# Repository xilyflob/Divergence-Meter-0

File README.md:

# Purpose
Recreate Tom Titor's original Divergence Meter project with more up to date hardware and software. Also taking into account current tools and services avalible to makers.

# Goals
* Maintain level of visual accuracy to the show that was in the original.
* Keep code size down so if people don't want to use updated hardware they can still fit it on the old chip.
  * Currently failing this, assembly output from the C code has proven much less efficient than I had anticipated.
* Provide more accessible code for the microcontroller so makers can make changes on their own easier than with the assembly version, also commented well enough that it is easy to understand.
* Produce at least proper drawings for the physical construction. Ideally a solid model as well, however there may be license issues with that.

# Software Used
* Autodesk Eagle
  * Originally used to do the PCB design, the SMT versions were later converted to KiCad. Earlier, simpler converts and redesigns currently remain in those file types.
* KiCad
* MPLAB X IDE
  * XC8 compiler
* Solidworks

# Build Log
Available on [Imgur](https://imgur.com/a/QL4b4lS), maybe one day I will make a website for better layout and such.

# Current Status 9/16/23
Long time no update :)

Lost lots of motivation to work on this after I realized that there are more I2C issues. Regular writes flat out dont work, you make it though the code but they don't take on the RTC. Currently implementing a fix that is reccomended in the 8803 manual, hopefully it works.

No changes to hardware this time, I do have a bunch of ideas for a Rev B including actually hooking up the INT line from the RTC which could prove EXTREMELY useful in making the software less "busy".

Motivation remains hard, hope to keep at this as well as I can.

# Background
Full disclosure time, I have zero formal training in coding or electrical engineering, I am actually a machinist (I guess that makes me qualified to fab the actual box though). On top of this, this is my first time doing any assembly reading, C coding, coding for microchips, or circuit board design. If I make a mistake that you see, PLEASE tell me.

I've wanted to do Tom's divergence meter project basically since I first found it after watching the Steins;Gate show. Never actually had the drive to do it though. Don't ask me why, but at some point in 2021 I went to look at the site, only to find it gone. Wayback Machine has an archive, but more importantly whoever the saint is that runs brotoro.com made a complete functional rehost of the site, which is much less clunky than Wayback. Would definitely say that almost losing that info really pushed me to start working on this.

# Thanks
* Jonathan from [SWISSNIXIE](http://www.swissnixie.com/) for helping me understand nixie tube amperage and resistance requirement as well as lending prototyping advice on the HV5623 drivers.
* John from [Taylor Electronics](https://www.shop-tes.com/) for providing data on the current usage of the 1364 HVPS in this specific application.
* /r/PrintedCircuitBoard for doing their best to answer my questions

# Licence
Hardware: Creative Commons Attribution-ShareAlike 4.0 International

Software: GNU GPL V3.0

Also just let me know if you use anything. Or if you make this! Would love to see people's projects.

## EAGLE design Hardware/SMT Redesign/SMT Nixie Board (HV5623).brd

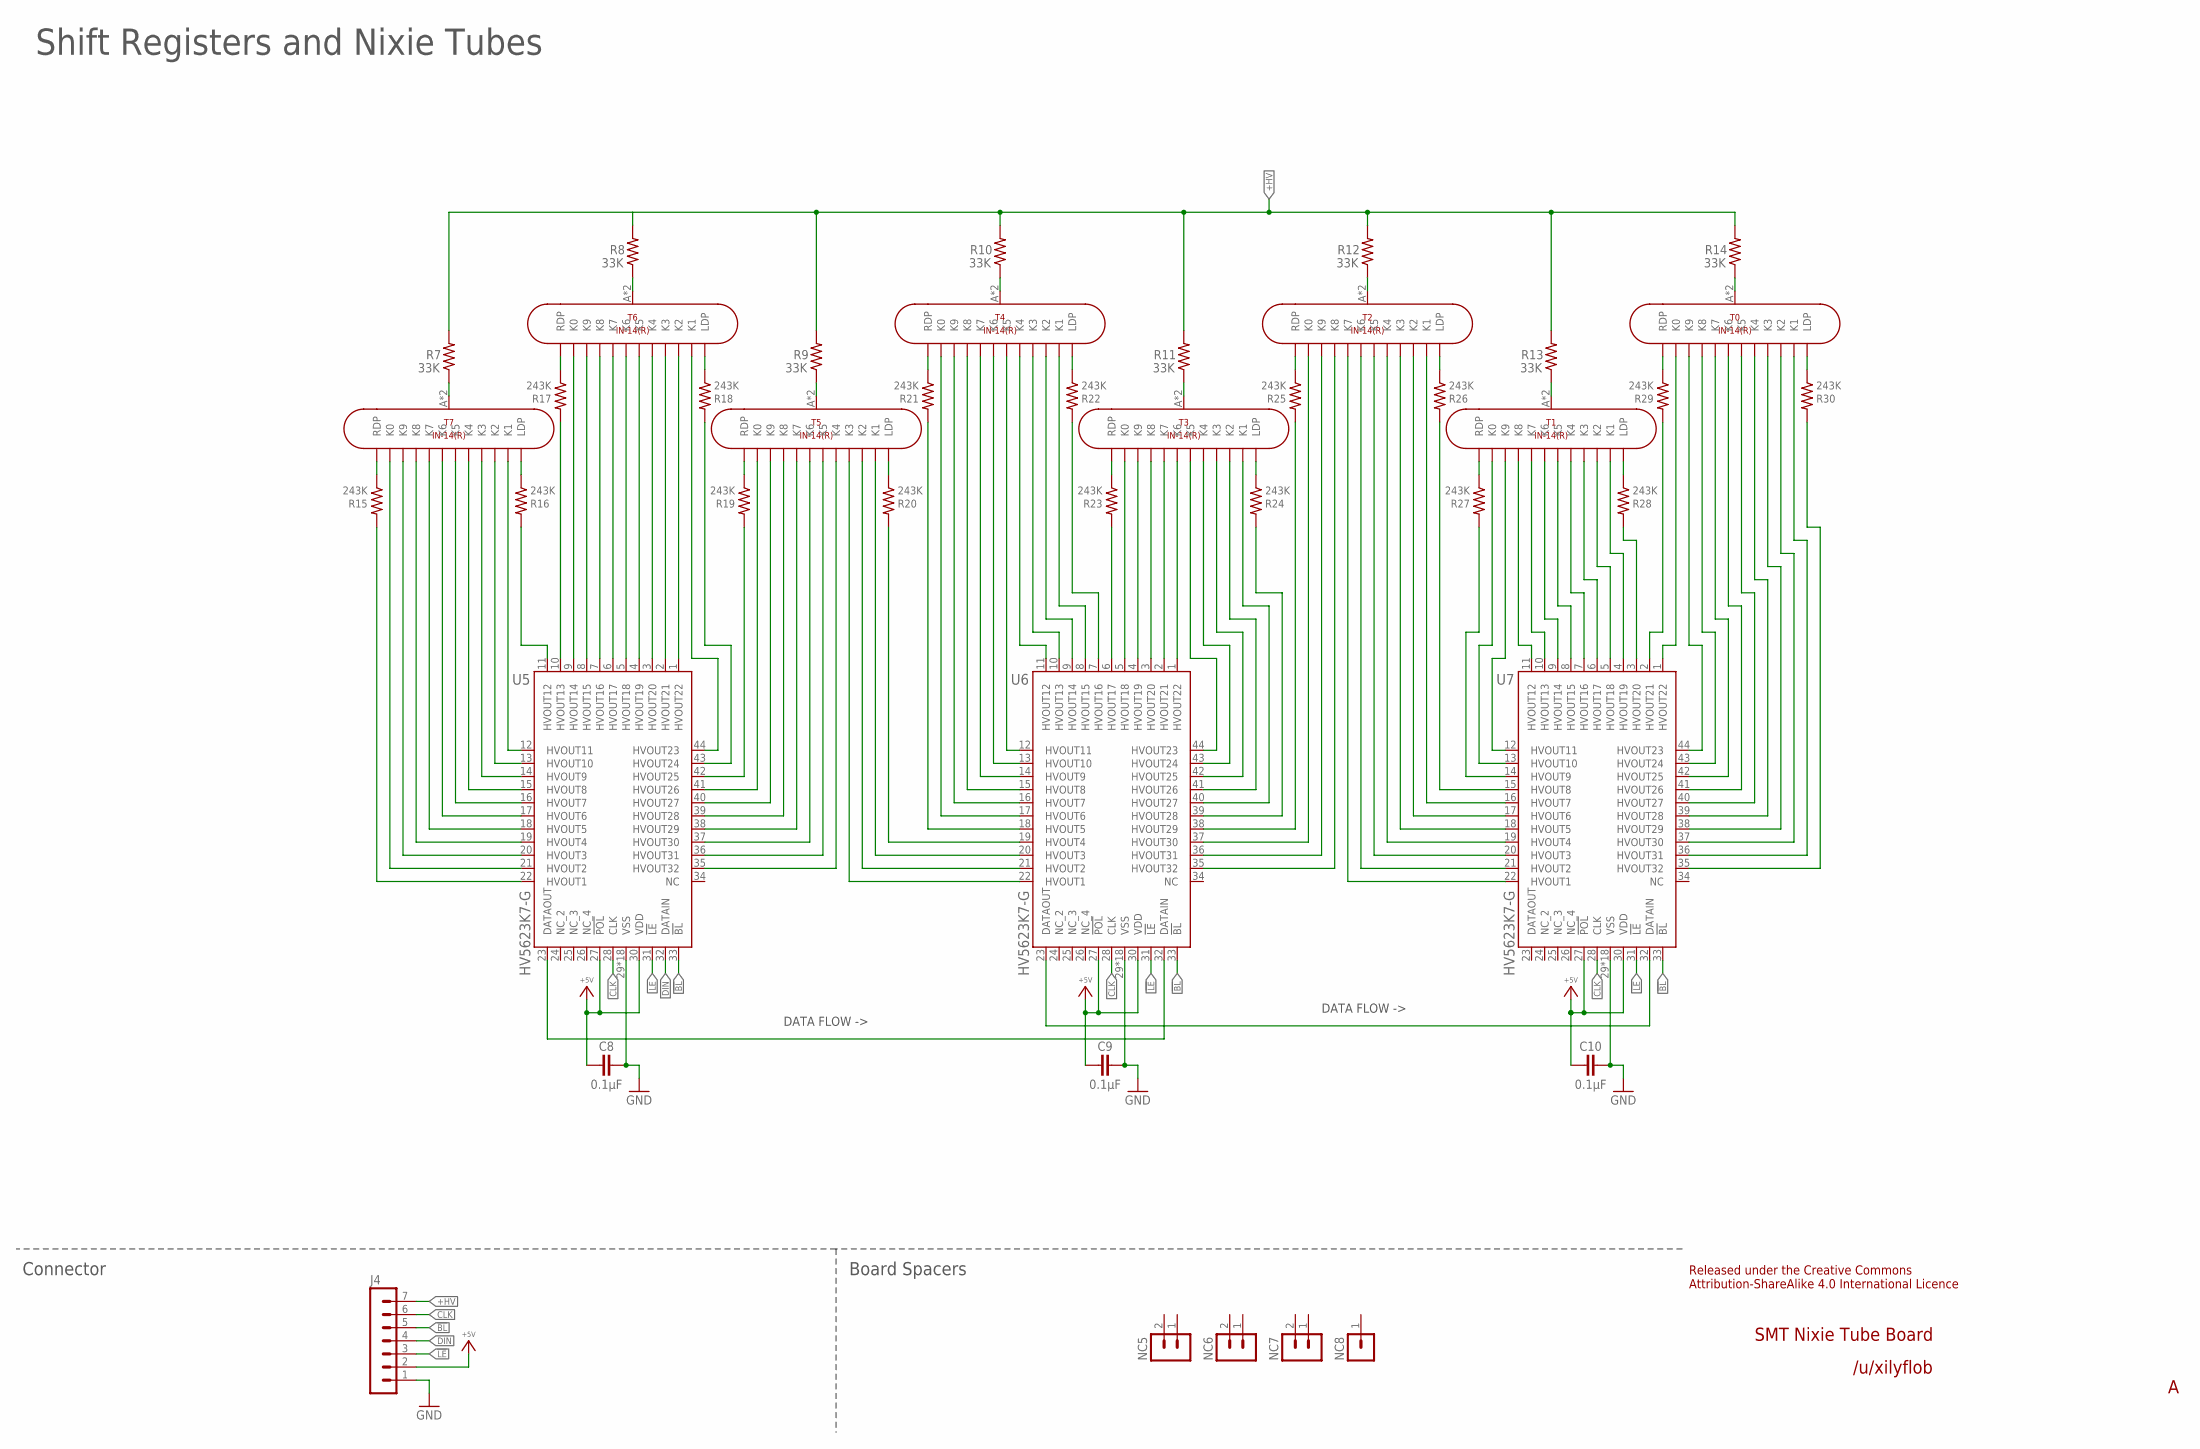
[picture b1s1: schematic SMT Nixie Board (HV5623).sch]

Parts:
C8, C9, C10: 0.1µF; C0805
J4: 1; MA07
NC5, NC6, NC7: MA02
NC8: MA01
R7, R8, R9, R10, R11, R12, R13, R14: 33K; R2512
R15, R16, R17, R18, R19, R20, R21, R22, R23, R24, R25, R26, R27, R28, R29, R30: 243K; R2010
T0, T1, T2, T3, T4, T5, T6, T7: IN-14(R); IN-14_REVERSE
U5, U6, U7: HV5623K7-G; WQFN-44

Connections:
!BL!: J4.5, U5.33 (!BL), U6.33 (!BL), U7.33 (!BL)
!LE!: J4.3, U5.31 (!LE), U6.31 (!LE), U7.31 (!LE)
+5V: C8.1, C9.1, C10.1, J4.2, U5.27 (!POL), U5.30 (VDD), U6.27 (!POL), U6.30 (VDD), U7.27 (!POL), U7.30 (VDD)
+HV: J4.7, R7.2, R8.2, R9.2, R10.2, R11.2, R12.2, R13.2, R14.2
CLK: J4.6, U5.28 (CLK), U6.28 (CLK), U7.28 (CLK)
DIN: J4.4, U5.32 (DATAIN)
GND: C8.2, C9.2, C10.2, J4.1, U5.29 (VSS), U5.P$1 (VSS), U5.P$2 (VSS), U5.P$3 (VSS), U5.P$4 (VSS), U5.P$5 (VSS), U5.P$6 (VSS), U5.P$7 (VSS), U5.P$8 (VSS), U5.P$9 (VSS), U5.P$10 (VSS), U5.P$11 (VSS), U5.P$12 (VSS), U5.P$13 (VSS), U5.P$14 (VSS), U5.P$15 (VSS), U5.P$16 (VSS), U5.TP (VSS), U6.29 (VSS), U6.P$1 (VSS), U6.P$2 (VSS), U6.P$3 (VSS), U6.P$4 (VSS), U6.P$5 (VSS), U6.P$6 (VSS), U6.P$7 (VSS), U6.P$8 (VSS), U6.P$9 (VSS), U6.P$10 (VSS), U6.P$11 (VSS), U6.P$12 (VSS), U6.P$13 (VSS), U6.P$14 (VSS), U6.P$15 (VSS), U6.P$16 (VSS), U6.TP (VSS), U7.29 (VSS), U7.P$1 (VSS), U7.P$2 (VSS), U7.P$3 (VSS), U7.P$4 (VSS), U7.P$5 (VSS), U7.P$6 (VSS), U7.P$7 (VSS), U7.P$8 (VSS), U7.P$9 (VSS), U7.P$10 (VSS), U7.P$11 (VSS), U7.P$12 (VSS), U7.P$13 (VSS), U7.P$14 (VSS), U7.P$15 (VSS), U7.P$16 (VSS), U7.TP (VSS)
T0A: R7.1, T7.A, T7.A_1 (A)
T1A: R8.1, T6.A, T6.A_1 (A)
T2A: R9.1, T5.A, T5.A_1 (A)
T3A: R10.1, T4.A, T4.A_1 (A)
T4A: R11.1, T3.A, T3.A_1 (A)
T5A: R12.1, T2.A, T2.A_1 (A)
T6A: R13.1, T1.A, T1.A_1 (A)
T7A: R14.1, T0.A, T0.A_1 (A)
U5-T0K0: T7.K0, T7.K0_1 (K0), U5.21 (HVOUT2)
U5-T0K1: T7.K1, T7.K1_1 (K1), U5.12 (HVOUT11)
U5-T0K2: T7.K2, T7.K2_1 (K2), U5.13 (HVOUT10)
U5-T0K3: T7.K3, T7.K3_1 (K3), U5.14 (HVOUT9)
U5-T0K4: T7.K4, T7.K4_1 (K4), U5.15 (HVOUT8)
U5-T0K5: T7.K5, T7.K5_1 (K5), U5.16 (HVOUT7)
U5-T0K6: T7.K6, T7.K6_1 (K6), U5.17 (HVOUT6)
U5-T0K7: T7.K7, T7.K7_1 (K7), U5.18 (HVOUT5)
U5-T0K8: T7.K8, T7.K8_1 (K8), U5.19 (HVOUT4)
U5-T0K9: T7.K9, T7.K9_1 (K9), U5.20 (HVOUT3)
U5-T0LDP: R16.2, U5.11 (HVOUT12)
U5-T0LDP1: R16.1, T7.LDP, T7.LDP_1 (LDP)
U5-T0RDP: R15.2, U5.22 (HVOUT1)
U5-T0RDP1: R15.1, T7.RDP, T7.RDP_1 (RDP)
U5-T1K0: T6.K0, T6.K0_1 (K0), U5.9 (HVOUT14)
U5-T1K1: T6.K1, T6.K1_1 (K1), U5.44 (HVOUT23)
U5-T1K2: T6.K2, T6.K2_1 (K2), U5.1 (HVOUT22)
U5-T1K3: T6.K3, T6.K3_1 (K3), U5.2 (HVOUT21)
U5-T1K4: T6.K4, T6.K4_1 (K4), U5.3 (HVOUT20)
U5-T1K5: T6.K5, T6.K5_1 (K5), U5.4 (HVOUT19)
U5-T1K6: T6.K6, T6.K6_1 (K6), U5.5 (HVOUT18)
U5-T1K7: T6.K7, T6.K7_1 (K7), U5.6 (HVOUT17)
U5-T1K8: T6.K8, T6.K8_1 (K8), U5.7 (HVOUT16)
U5-T1K9: T6.K9, T6.K9_1 (K9), U5.8 (HVOUT15)
U5-T1LDP: R18.2, U5.43 (HVOUT24)
U5-T1LDP1: R18.1, T6.LDP, T6.LDP_1 (LDP)
U5-T1RDP: R17.2, U5.10 (HVOUT13)
U5-T1RDP1: R17.1, T6.RDP, T6.RDP_1 (RDP)
U5-T2K0: T5.K0, T5.K0_1 (K0), U5.41 (HVOUT26)
U5-T2K4: T5.K4, T5.K4_1 (K4), U5.35 (HVOUT32)
U5-T2K5: T5.K5, T5.K5_1 (K5), U5.36 (HVOUT31)
U5-T2K6: T5.K6, T5.K6_1 (K6), U5.37 (HVOUT30)
U5-T2K7: T5.K7, T5.K7_1 (K7), U5.38 (HVOUT29)
U5-T2K8: T5.K8, T5.K8_1 (K8), U5.39 (HVOUT28)
U5-T2K9: T5.K9, T5.K9_1 (K9), U5.40 (HVOUT27)
U5-T2RDP: R19.2, U5.42 (HVOUT25)
U5-T2RDP1: R19.1, T5.RDP, T5.RDP_1 (RDP)
U5-U6: U5.23 (DATAOUT), U6.32 (DATAIN)
U6-T2K1: T5.K1, T5.K1_1 (K1), U6.20 (HVOUT3)
U6-T2K2: T5.K2, T5.K2_1 (K2), U6.21 (HVOUT2)
U6-T2K3: T5.K3, T5.K3_1 (K3), U6.22 (HVOUT1)
U6-T2LDP: R20.2, U6.19 (HVOUT4)
U6-T2LDP1: R20.1, T5.LDP, T5.LDP_1 (LDP)
U6-T3K0: T4.K0, T4.K0_1 (K0), U6.17 (HVOUT6)
U6-T3K1: T4.K1, T4.K1_1 (K1), U6.8 (HVOUT15)
U6-T3K2: T4.K2, T4.K2_1 (K2), U6.9 (HVOUT14)
U6-T3K3: T4.K3, T4.K3_1 (K3), U6.10 (HVOUT13)
U6-T3K4: T4.K4, T4.K4_1 (K4), U6.11 (HVOUT12)
U6-T3K5: T4.K5, T4.K5_1 (K5), U6.12 (HVOUT11)
U6-T3K6: T4.K6, T4.K6_1 (K6), U6.13 (HVOUT10)
U6-T3K7: T4.K7, T4.K7_1 (K7), U6.14 (HVOUT9)
U6-T3K8: T4.K8, T4.K8_1 (K8), U6.15 (HVOUT8)
U6-T3K9: T4.K9, T4.K9_1 (K9), U6.16 (HVOUT7)
U6-T3LDP: R22.2, U6.7 (HVOUT16)
U6-T3LDP1: R22.1, T4.LDP, T4.LDP_1 (LDP)
U6-T3RDP: R21.2, U6.18 (HVOUT5)
U6-T3RDP1: R21.1, T4.RDP, T4.RDP_1 (RDP)
U6-T4K0: T3.K0, T3.K0_1 (K0), U6.5 (HVOUT18)
U6-T4K1: T3.K1, T3.K1_1 (K1), U6.40 (HVOUT27)
U6-T4K2: T3.K2, T3.K2_1 (K2), U6.41 (HVOUT26)
U6-T4K3: T3.K3, T3.K3_1 (K3), U6.42 (HVOUT25)
U6-T4K4: T3.K4, T3.K4_1 (K4), U6.43 (HVOUT24)
U6-T4K5: T3.K5, T3.K5_1 (K5), U6.44 (HVOUT23)
U6-T4K6: T3.K6, T3.K6_1 (K6), U6.1 (HVOUT22)
U6-T4K7: T3.K7, T3.K7_1 (K7), U6.2 (HVOUT21)
U6-T4K8: T3.K8, T3.K8_1 (K8), U6.3 (HVOUT20)
U6-T4K9: T3.K9, T3.K9_1 (K9), U6.4 (HVOUT19)
U6-T4LDP: R24.2, U6.39 (HVOUT28)
U6-T4LDP1: R24.1, T3.LDP, T3.LDP_1 (LDP)
U6-T4RDP: R23.2, U6.6 (HVOUT17)
U6-T4RDP1: R23.1, T3.RDP, T3.RDP_1 (RDP)
U6-T5K0: T2.K0, T2.K0_1 (K0), U6.37 (HVOUT30)
U6-T5K8: T2.K8, T2.K8_1 (K8), U6.35 (HVOUT32)
U6-T5K9: T2.K9, T2.K9_1 (K9), U6.36 (HVOUT31)
U6-T5RDP: R25.2, U6.38 (HVOUT29)
U6-T5RDP1: R25.1, T2.RDP, T2.RDP_1 (RDP)
U6-U7: U6.23 (DATAOUT), U7.32 (DATAIN)
U7-T5K1: T2.K1, T2.K1_1 (K1), U7.16 (HVOUT7)
U7-T5K2: T2.K2, T2.K2_1 (K2), U7.17 (HVOUT6)
U7-T5K3: T2.K3, T2.K3_1 (K3), U7.18 (HVOUT5)
U7-T5K4: T2.K4, T2.K4_1 (K4), U7.19 (HVOUT4)
U7-T5K5: T2.K5, T2.K5_1 (K5), U7.20 (HVOUT3)
U7-T5K6: T2.K6, T2.K6_1 (K6), U7.21 (HVOUT2)
U7-T5K7: T2.K7, T2.K7_1 (K7), U7.22 (HVOUT1)
U7-T5LDP: R26.2, U7.15 (HVOUT8)
U7-T5LDP1: R26.1, T2.LDP, T2.LDP_1 (LDP)
U7-T6K0: T1.K0, T1.K0_1 (K0), U7.13 (HVOUT10)
U7-T6K1: T1.K1, T1.K1_1 (K1), U7.4 (HVOUT19)
U7-T6K2: T1.K2, T1.K2_1 (K2), U7.5 (HVOUT18)
U7-T6K3: T1.K3, T1.K3_1 (K3), U7.6 (HVOUT17)
U7-T6K4: T1.K4, T1.K4_1 (K4), U7.7 (HVOUT16)
U7-T6K5: T1.K5, T1.K5_1 (K5), U7.8 (HVOUT15)
U7-T6K6: T1.K6, T1.K6_1 (K6), U7.9 (HVOUT14)
U7-T6K7: T1.K7, T1.K7_1 (K7), U7.10 (HVOUT13)
U7-T6K8: T1.K8, T1.K8_1 (K8), U7.11 (HVOUT12)
U7-T6K9: T1.K9, T1.K9_1 (K9), U7.12 (HVOUT11)
U7-T6LDP: R28.2, U7.3 (HVOUT20)
U7-T6LDP1: R28.1, T1.LDP, T1.LDP_1 (LDP)
U7-T6RDP: R27.2, U7.14 (HVOUT9)
U7-T6RDP1: R27.1, T1.RDP, T1.RDP_1 (RDP)
U7-T7K0: T0.K0, T0.K0_1 (K0), U7.1 (HVOUT22)
U7-T7K1: T0.K1, T0.K1_1 (K1), U7.36 (HVOUT31)
U7-T7K2: T0.K2, T0.K2_1 (K2), U7.37 (HVOUT30)
U7-T7K3: T0.K3, T0.K3_1 (K3), U7.38 (HVOUT29)
U7-T7K4: T0.K4, T0.K4_1 (K4), U7.39 (HVOUT28)
U7-T7K5: T0.K5, T0.K5_1 (K5), U7.40 (HVOUT27)
U7-T7K6: T0.K6, T0.K6_1 (K6), U7.41 (HVOUT26)
U7-T7K7: T0.K7, T0.K7_1 (K7), U7.42 (HVOUT25)
U7-T7K8: T0.K8, T0.K8_1 (K8), U7.43 (HVOUT24)
U7-T7K9: T0.K9, T0.K9_1 (K9), U7.44 (HVOUT23)
U7-T7LDP: R30.2, U7.35 (HVOUT32)
U7-T7LDP1: R30.1, T0.LDP, T0.LDP_1 (LDP)
U7-T7RDP: R29.2, U7.2 (HVOUT21)
U7-T7RDP1: R29.1, T0.RDP, T0.RDP_1 (RDP)

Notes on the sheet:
/u/xilyflob
Released under the Creative Commons Attribution-ShareAlike 4.0 International Licence
SMT Nixie Tube Board
Shift Registers and Nixie Tubes
Connector
Board Spacers
DATA FLOW ->

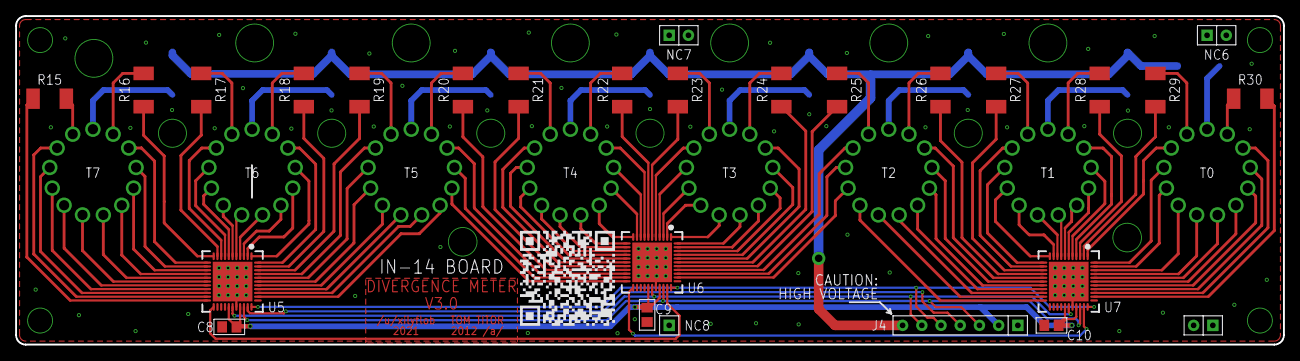
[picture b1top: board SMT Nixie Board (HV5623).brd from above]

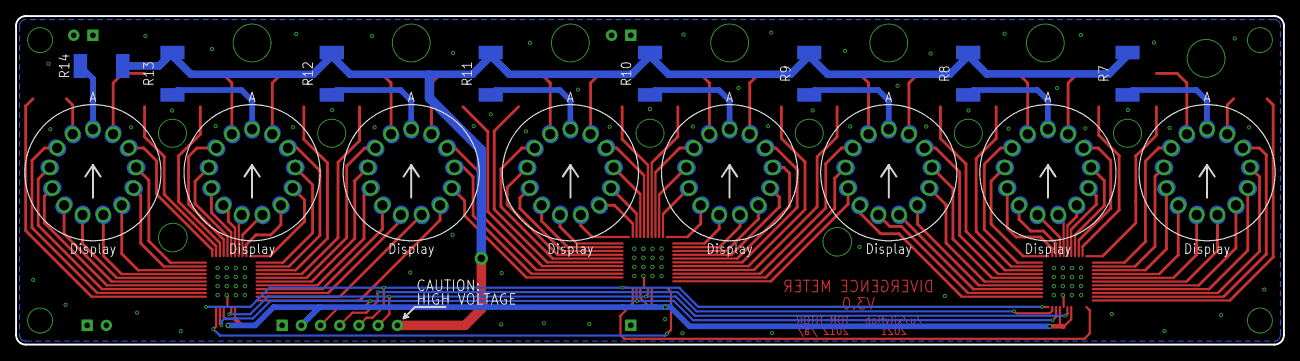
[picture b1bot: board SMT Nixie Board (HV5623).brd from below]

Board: 2 copper layers, 167.6 x 43.4 mm, 43 parts (16 on the bottom side), 129 nets.

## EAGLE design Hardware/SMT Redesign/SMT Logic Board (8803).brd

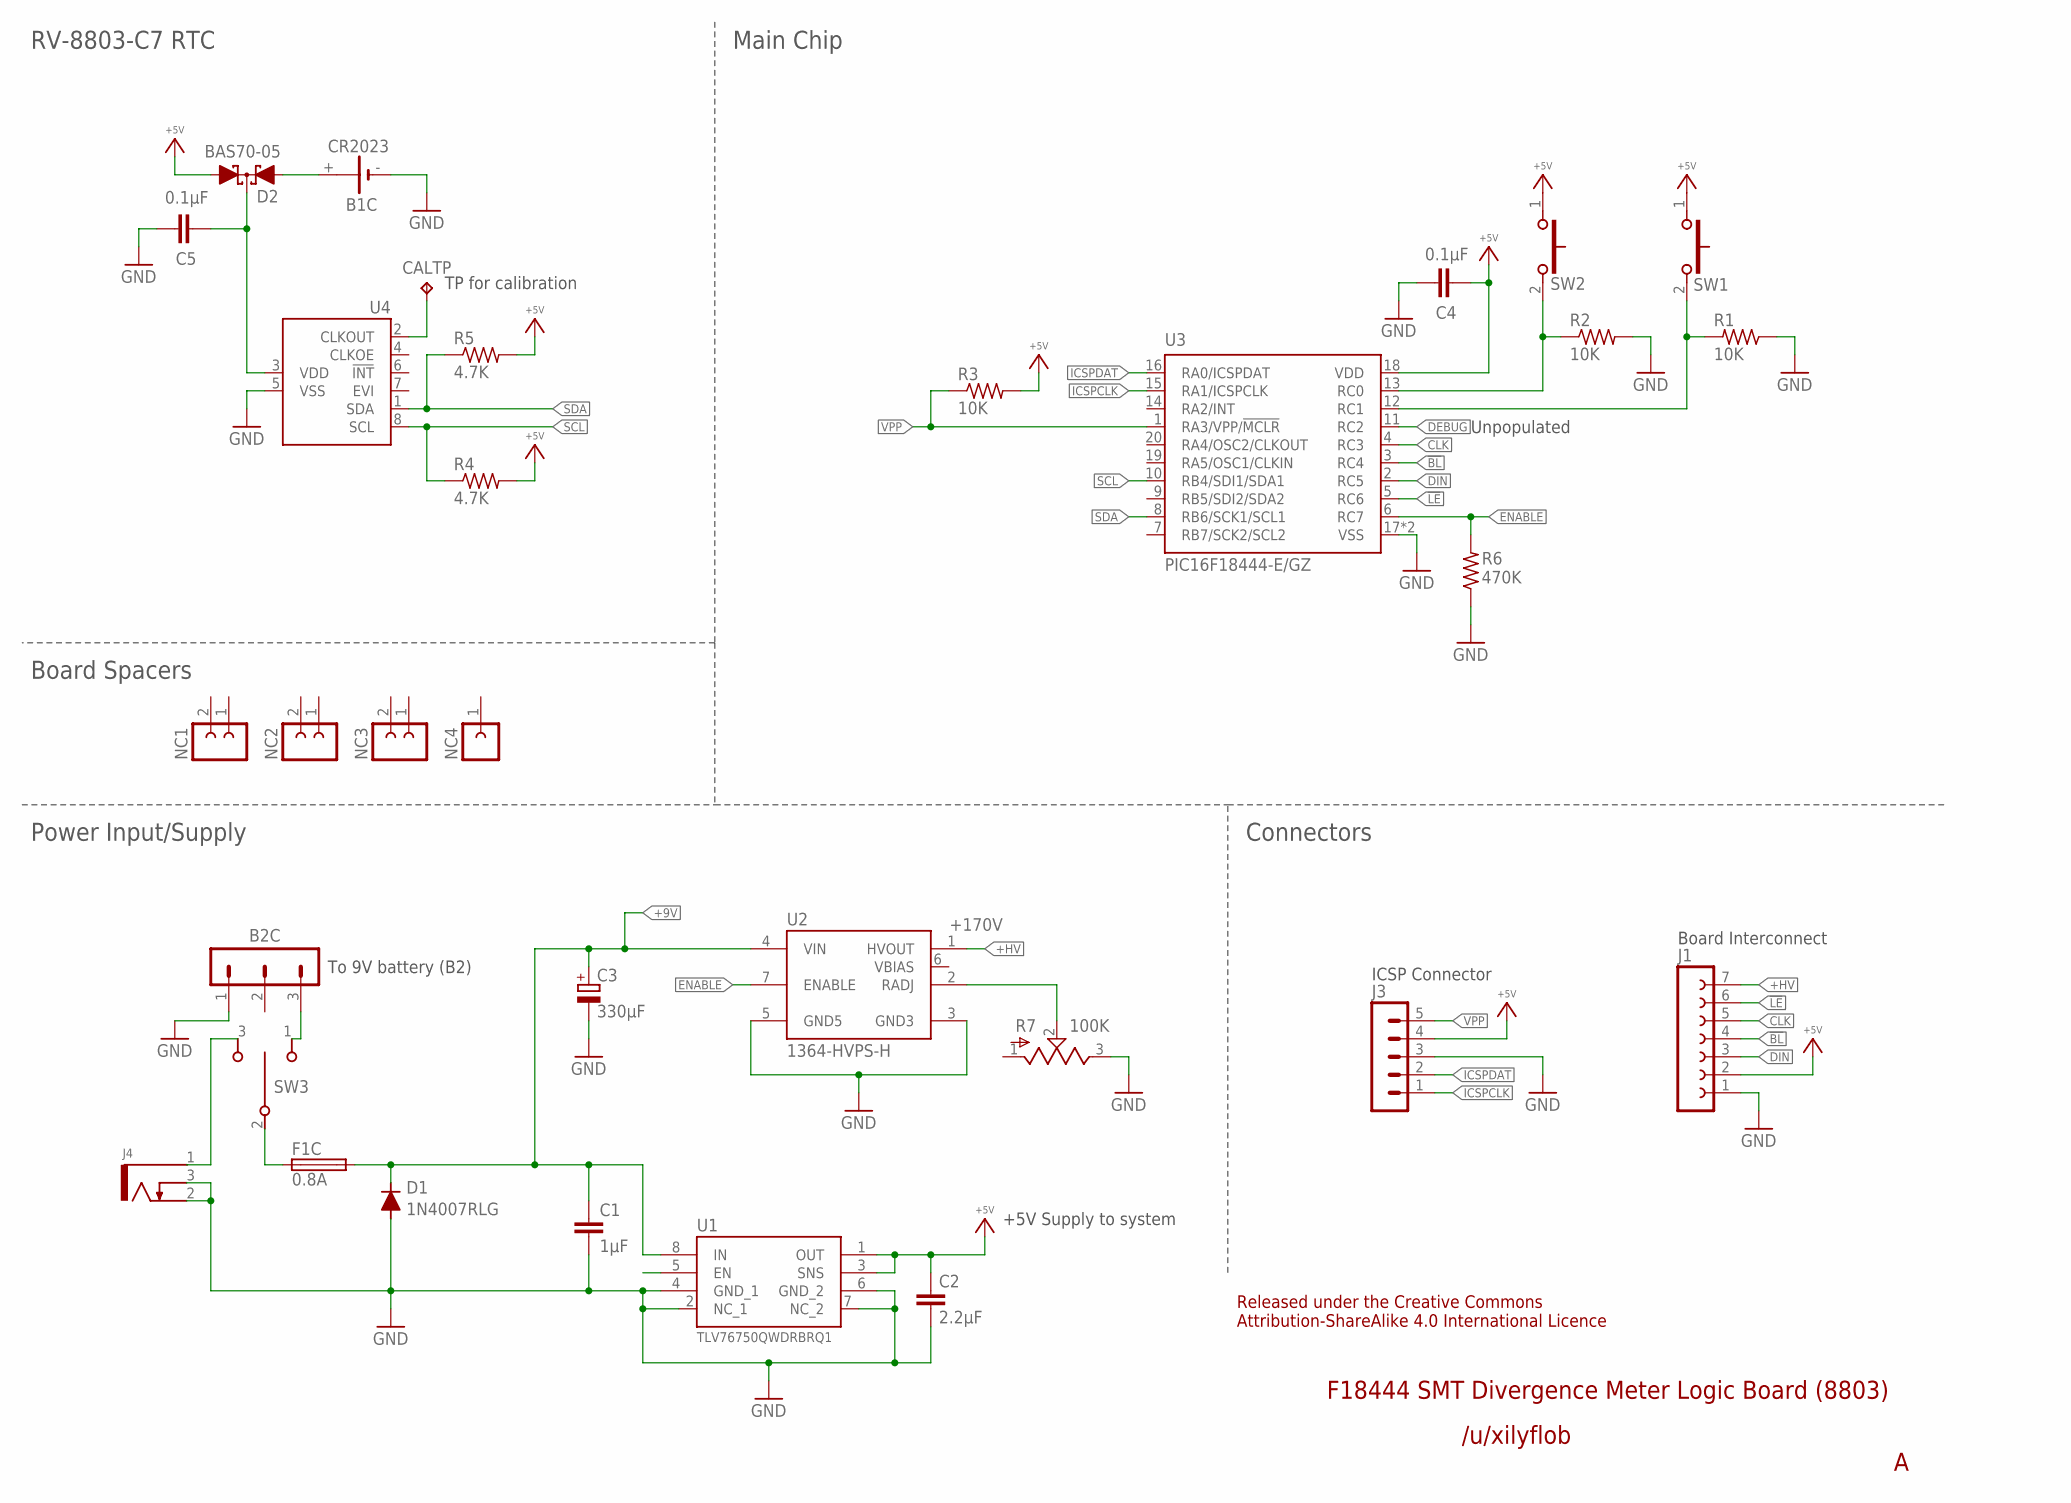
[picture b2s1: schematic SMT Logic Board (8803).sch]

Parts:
B1C: CR2023; 103
B2C: 53253_3P; 532530370
C1: 1µF; C0805
C2: 2.2μF; C0805
C3: 330µF; 6.3MM_SMD_CHIP
C4, C5: 0.1µF; C0805
CALTP: TPTP18R; TP18R
D1: 1N4007RLG; SMA-403D
D2: BAS70-05; SOT323
F1C: 0.8A; 5X20MM
J1: FE07FE07; FE07
J3: MA05
J4: KLDX-0202-B; KDLX-0202-X
NC1, NC2, NC3: FE02
NC4: FE01
R1, R2, R3: 10K; R0805
R4, R5: 4.7K; R0805
R6: 470K; R0805
R7: 100K; 3224W
SW1, SW2: FSMRA4JH04; FSMRA4JH
SW3: 5MS1S102AM6QES; SLIDE_SPDT_MINI
U1: TLV76750QWDRBRQ1; SON_8_FIXED
U2: 1364-HVPS-H
U3: PIC16F18444-E/GZ; UQFN-20
U4: RV-8803-C7; C7

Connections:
!BL!: J1.4, U3.3 (RC4)
!LE!: J1.6, U3.5 (RC6)
+5V: C2.1, C4.1, D2.2 (A2), J1.2, J3.4, R3.2, R4.2, R5.2, SW1.1, SW2.1, U1.1 (OUT), U1.3 (SNS), U3.18 (VDD)
+9V: C1.1, C3.+, D1.C, F1C.2A (2), F1C.2B (2), U1.8 (IN), U2.4 (VIN)
+9V_1: F1C.1A (1), F1C.1B (1), SW3.2 (COM)
+9V_2: J4.1, SW3.3 (POS_2)
+9V_3: B2C.3, SW3.1 (POS_1)
+HV: J1.7, U2.1 (HVOUT)
CLK: J1.5, U3.4 (RC3)
CLKTEST: CALTP.TP, U4.2 (CLKOUT)
DEBUG: U3.11 (RC2)
DIN: J1.3, U3.2 (RC5)
EN: U1.5 (EN)
ENABLE: R6.2, U2.7 (ENABLE), U3.6 (RC7)
GND: B1C.-, B2C.1, C1.2, C2.2, C3.-, C4.2, C5.2, D1.A, J1.1, J3.3, J4.2, J4.3, R1.1, R2.2, R6.1, R7.3, U1.2 (NC_1), U1.4 (GND_1), U1.6 (GND_2), U1.7 (NC_2), U1.TP, U1.TV_1 (TP), U1.TV_2 (TP), U1.TV_3 (TP), U1.TV_4 (TP), U1.TV_5 (TP), U1.TV_6 (TP), U1.TV_7 (TP), U1.TV_8 (TP), U1.TV_9 (TP), U2.3 (GND3), U2.5 (GND5), U3.17 (VSS), U3.21 (VSS), U4.5 (VSS)
ICSPCLK: J3.1, U3.15 (RA1/ICSPCLK)
ICSPDAT: J3.2, U3.16 (RA0/ICSPDAT)
RADJ: R7.2, U2.2 (RADJ)
RTCPWR: C5.1, D2.3 (C), U4.3 (VDD)
SCL: R4.1, U3.10 (RB4/SDI1/SDA1), U4.8 (SCL)
SDA: R5.1, U3.8 (RB6/SCK1/SCL1), U4.1 (SDA)
SW1: R1.2, SW1.2, U3.12 (RC1)
SW2: R2.1, SW2.2, U3.13 (RC0)
VBAK: B1C.+, D2.1 (A1)
VPP: J3.5, R3.1, U3.1 (RA3/VPP/!MCLR!)

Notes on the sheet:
+170V
To 9V battery (B2)
RV-8803-C7 RTC
Connectors
Board Spacers
Power Input/Supply
Main Chip
/u/xilyflob
Released under the Creative Commons Attribution-ShareAlike 4.0 International Licence
F18444 SMT Divergence Meter Logic Board (8803)
+5V Supply to system
Unpopulated
Board Interconnect
ICSP Connector
TP for calibration

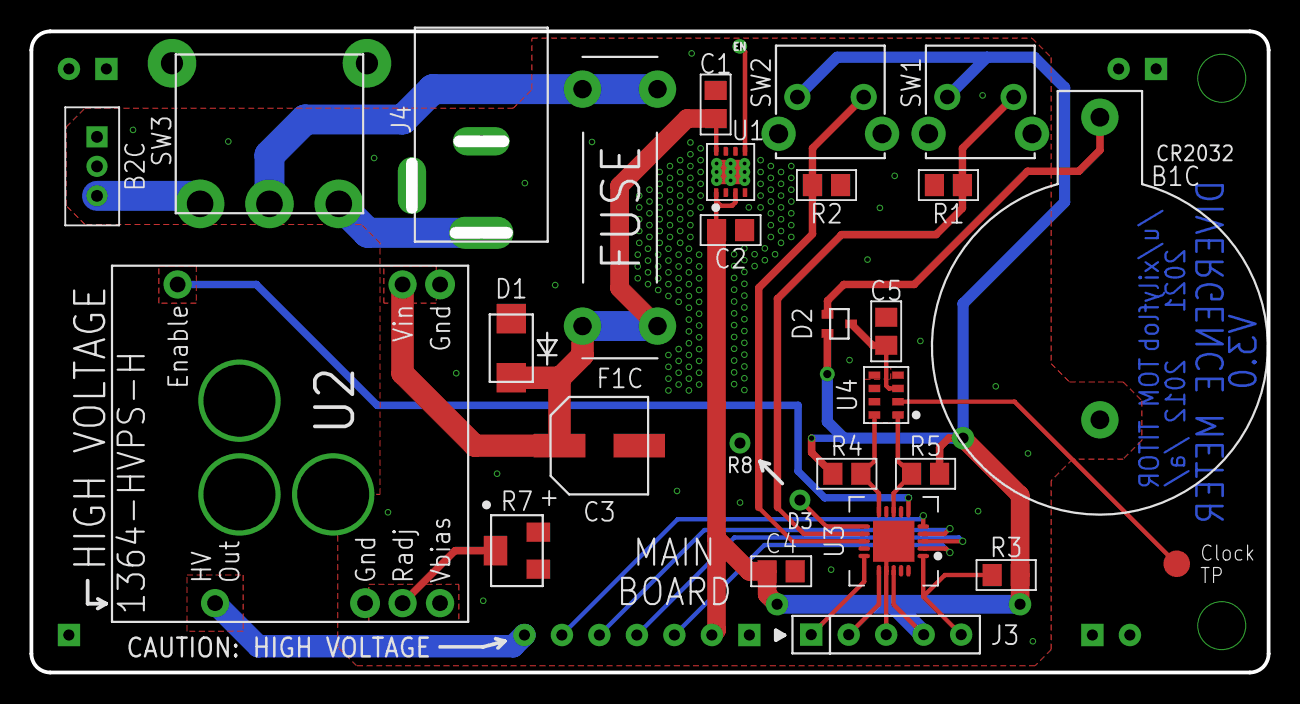
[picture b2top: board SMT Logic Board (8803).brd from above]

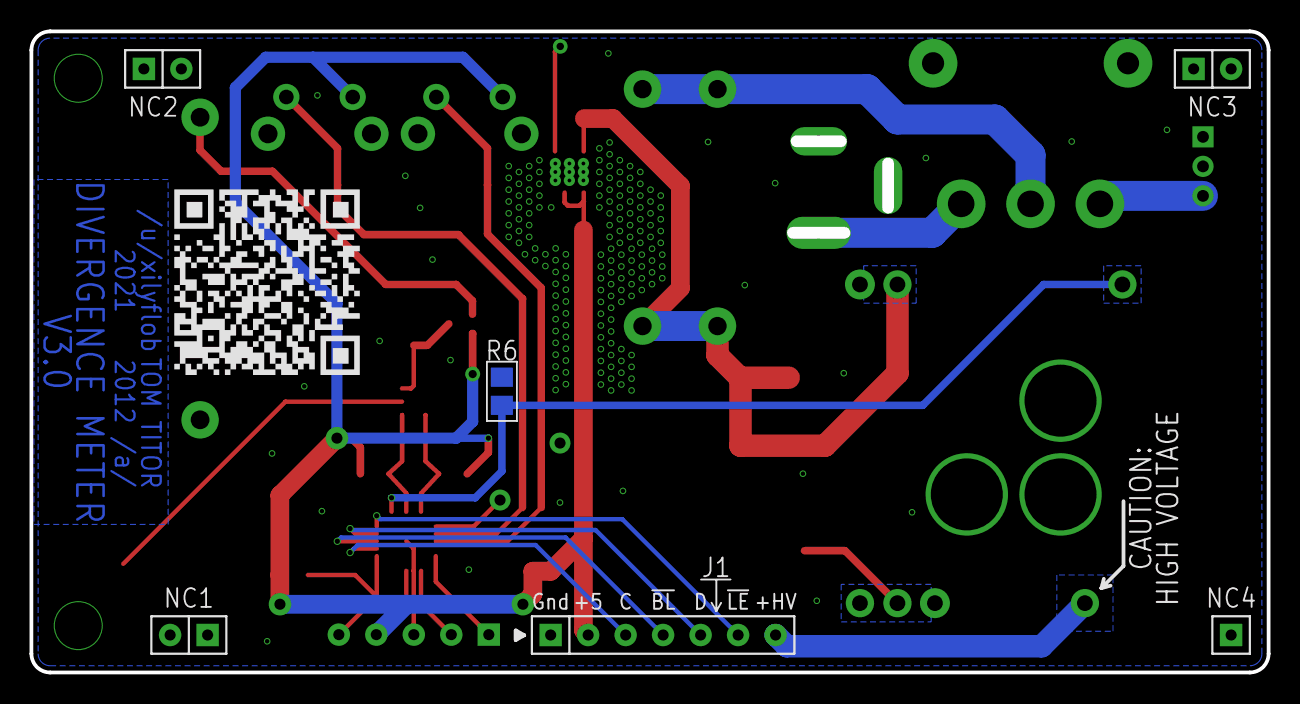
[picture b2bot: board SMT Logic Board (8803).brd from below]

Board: 2 copper layers, 83.8 x 43.4 mm, 32 parts (6 on the bottom side), 23 nets.

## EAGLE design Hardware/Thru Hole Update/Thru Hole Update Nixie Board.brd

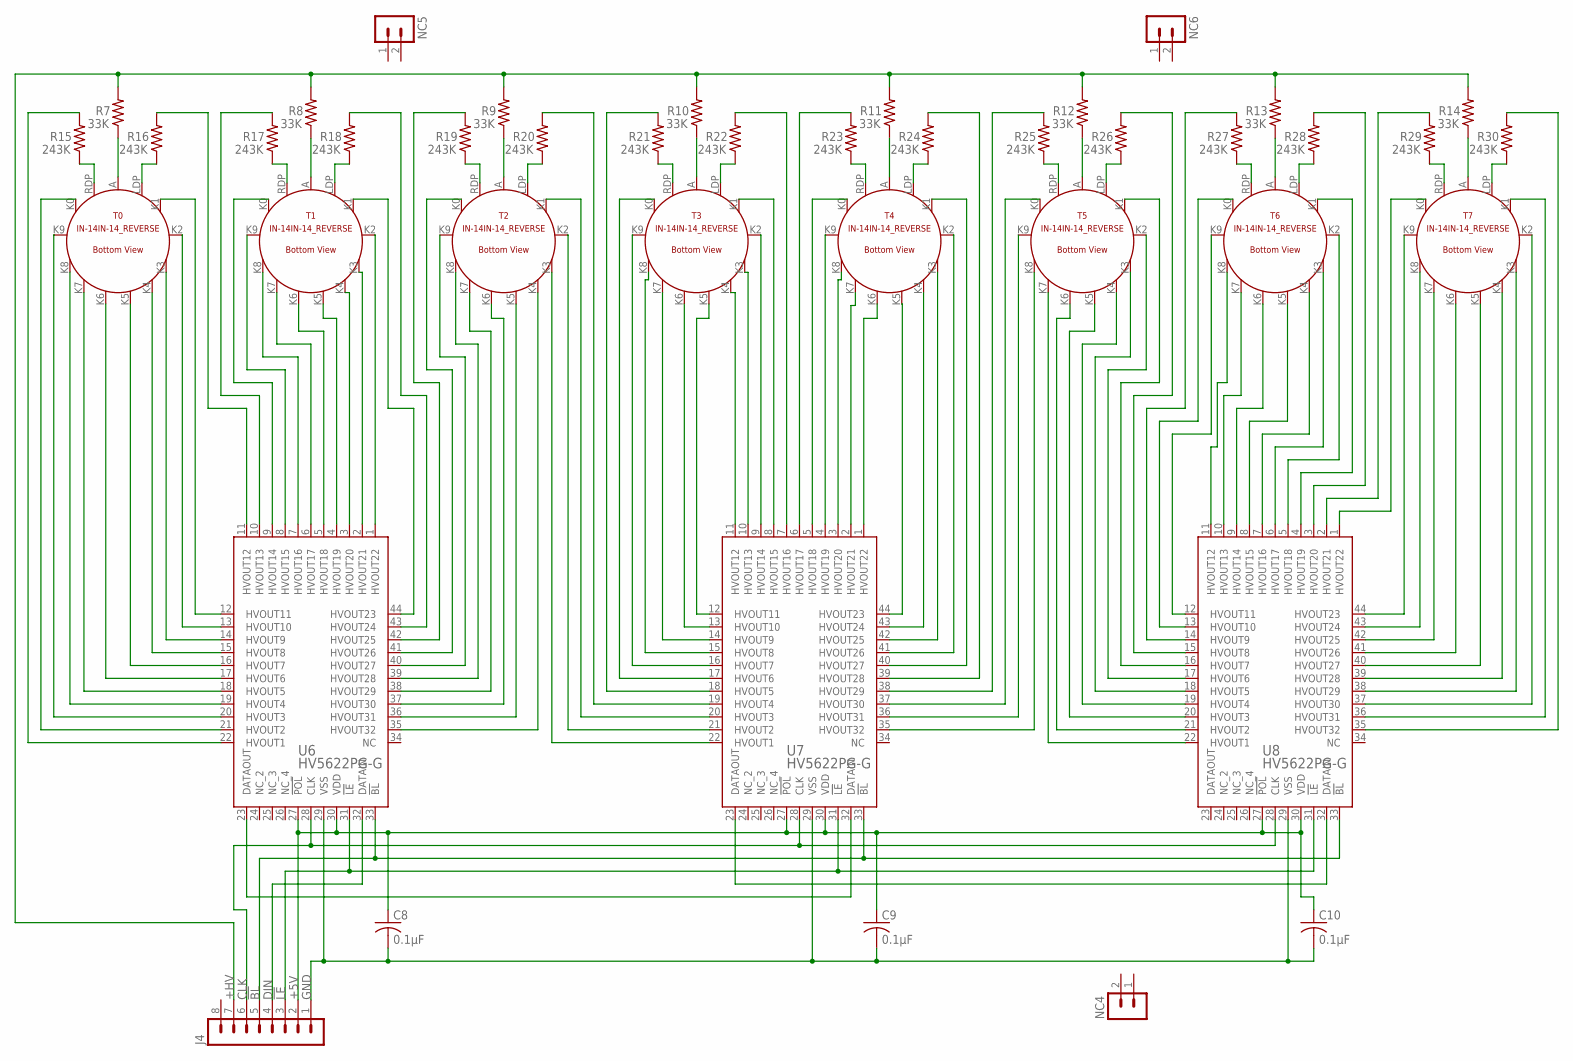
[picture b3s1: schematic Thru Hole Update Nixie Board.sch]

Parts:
C8, C9, C10: 0.1µF; C025-040X050
J4: 1; MA08
NC4, NC5, NC6: MA02
R7, R8, R9, R10, R11, R12, R13, R14: 33K; 0207/10
R15, R16, R17, R18, R19, R20, R21, R22, R23, R24, R25, R26, R27, R28, R29, R30: 243K; 0207/10
T0, T1, T2, T3, T4, T5, T6, T7: IN-14IN-14_REVERSE; IN-14_REVERSE
U6, U7, U8: HV5622PG-G; QFP-44

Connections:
!BL!: J4.5, U6.33 (!BL), U7.33 (!BL), U8.33 (!BL)
!LE!: J4.3, U6.31 (!LE), U7.31 (!LE), U8.31 (!LE)
+5V: C8.1, C9.1, C10.1, J4.2, U6.27 (!POL), U6.30 (VDD), U7.27 (!POL), U7.30 (VDD), U8.27 (!POL), U8.30 (VDD)
+HV: J4.7, R7.2, R8.2, R9.2, R10.2, R11.2, R12.2, R13.2, R14.2
CLK: J4.6, U6.28 (CLK), U7.28 (CLK), U8.28 (CLK)
DIN: J4.4, U6.32 (DATAIN)
GND: C8.2, C9.2, C10.2, J4.1, U6.29 (VSS), U7.29 (VSS), U8.29 (VSS)
T0A: R7.1, T0.A
T1A: R8.1, T1.A
T2A: R9.1, T2.A
T3A: R10.1, T3.A
T4A: R11.1, T4.A
T5A: R12.1, T5.A
T6A: R13.1, T6.A
T7A: R14.1, T7.A
U5-T0K0: T0.K0, U6.21 (HVOUT2)
U5-T0K1: T0.K1, U6.12 (HVOUT11)
U5-T0K2: T0.K2, U6.13 (HVOUT10)
U5-T0K3: T0.K3, U6.14 (HVOUT9)
U5-T0K4: T0.K4, U6.15 (HVOUT8)
U5-T0K5: T0.K5, U6.16 (HVOUT7)
U5-T0K6: T0.K6, U6.17 (HVOUT6)
U5-T0K7: T0.K7, U6.18 (HVOUT5)
U5-T0K8: T0.K8, U6.19 (HVOUT4)
U5-T0K9: T0.K9, U6.20 (HVOUT3)
U5-T0LDP: R16.2, U6.11 (HVOUT12)
U5-T0LDP1: R16.1, T0.LDP
U5-T0RDP: R15.2, U6.22 (HVOUT1)
U5-T0RDP1: R15.1, T0.RDP
U5-T1K0: T1.K0, U6.9 (HVOUT14)
U5-T1K1: T1.K1, U6.44 (HVOUT23)
U5-T1K2: T1.K2, U6.1 (HVOUT22)
U5-T1K3: T1.K3, U6.2 (HVOUT21)
U5-T1K4: T1.K4, U6.3 (HVOUT20)
U5-T1K5: T1.K5, U6.4 (HVOUT19)
U5-T1K6: T1.K6, U6.5 (HVOUT18)
U5-T1K7: T1.K7, U6.6 (HVOUT17)
U5-T1K8: T1.K8, U6.7 (HVOUT16)
U5-T1K9: T1.K9, U6.8 (HVOUT15)
U5-T1LDP: R18.2, U6.43 (HVOUT24)
U5-T1LDP1: R18.1, T1.LDP
U5-T1RDP: R17.2, U6.10 (HVOUT13)
U5-T1RDP1: R17.1, T1.RDP
U5-T2K0: T2.K0, U6.41 (HVOUT26)
U5-T2K4: T2.K4, U6.35 (HVOUT32)
U5-T2K5: T2.K5, U6.36 (HVOUT31)
U5-T2K6: T2.K6, U6.37 (HVOUT30)
U5-T2K7: T2.K7, U6.38 (HVOUT29)
U5-T2K8: T2.K8, U6.39 (HVOUT28)
U5-T2K9: T2.K9, U6.40 (HVOUT27)
U5-T2RDP: R19.2, U6.42 (HVOUT25)
U5-T2RDP1: R19.1, T2.RDP
U5-U6: U6.23 (DATAOUT), U7.32 (DATAIN)
U6-T2K1: T2.K1, U7.20 (HVOUT3)
U6-T2K2: T2.K2, U7.21 (HVOUT2)
U6-T2K3: T2.K3, U7.22 (HVOUT1)
U6-T2LDP: R20.2, U7.19 (HVOUT4)
U6-T2LDP1: R20.1, T2.LDP
U6-T3K0: T3.K0, U7.17 (HVOUT6)
U6-T3K1: T3.K1, U7.8 (HVOUT15)
U6-T3K2: T3.K2, U7.9 (HVOUT14)
U6-T3K3: T3.K3, U7.10 (HVOUT13)
U6-T3K4: T3.K4, U7.11 (HVOUT12)
U6-T3K5: T3.K5, U7.12 (HVOUT11)
U6-T3K6: T3.K6, U7.13 (HVOUT10)
U6-T3K7: T3.K7, U7.14 (HVOUT9)
U6-T3K8: T3.K8, U7.15 (HVOUT8)
U6-T3K9: T3.K9, U7.16 (HVOUT7)
U6-T3LDP: R22.2, U7.7 (HVOUT16)
U6-T3LDP1: R22.1, T3.LDP
U6-T3RDP: R21.2, U7.18 (HVOUT5)
U6-T3RDP1: R21.1, T3.RDP
U6-T4K0: T4.K0, U7.5 (HVOUT18)
U6-T4K1: T4.K1, U7.40 (HVOUT27)
U6-T4K2: T4.K2, U7.41 (HVOUT26)
U6-T4K3: T4.K3, U7.42 (HVOUT25)
U6-T4K4: T4.K4, U7.43 (HVOUT24)
U6-T4K5: T4.K5, U7.44 (HVOUT23)
U6-T4K6: T4.K6, U7.1 (HVOUT22)
U6-T4K7: T4.K7, U7.2 (HVOUT21)
U6-T4K8: T4.K8, U7.3 (HVOUT20)
U6-T4K9: T4.K9, U7.4 (HVOUT19)
U6-T4LDP: R24.2, U7.39 (HVOUT28)
U6-T4LDP1: R24.1, T4.LDP
U6-T4RDP: R23.2, U7.6 (HVOUT17)
U6-T4RDP1: R23.1, T4.RDP
U6-T5K0: T5.K0, U7.37 (HVOUT30)
U6-T5K8: T5.K8, U7.35 (HVOUT32)
U6-T5K9: T5.K9, U7.36 (HVOUT31)
U6-T5RDP: R25.2, U7.38 (HVOUT29)
U6-T5RDP1: R25.1, T5.RDP
U6-U7: U7.23 (DATAOUT), U8.32 (DATAIN)
U7-T5K1: T5.K1, U8.16 (HVOUT7)
U7-T5K2: T5.K2, U8.17 (HVOUT6)
U7-T5K3: T5.K3, U8.18 (HVOUT5)
U7-T5K4: T5.K4, U8.19 (HVOUT4)
U7-T5K5: T5.K5, U8.20 (HVOUT3)
U7-T5K6: T5.K6, U8.21 (HVOUT2)
U7-T5K7: T5.K7, U8.22 (HVOUT1)
U7-T5LDP: R26.2, U8.15 (HVOUT8)
U7-T5LDP1: R26.1, T5.LDP
U7-T6K0: T6.K0, U8.13 (HVOUT10)
U7-T6K1: T6.K1, U8.4 (HVOUT19)
U7-T6K2: T6.K2, U8.5 (HVOUT18)
U7-T6K3: T6.K3, U8.6 (HVOUT17)
U7-T6K4: T6.K4, U8.7 (HVOUT16)
U7-T6K5: T6.K5, U8.8 (HVOUT15)
U7-T6K6: T6.K6, U8.9 (HVOUT14)
U7-T6K7: T6.K7, U8.10 (HVOUT13)
U7-T6K8: T6.K8, U8.11 (HVOUT12)
U7-T6K9: T6.K9, U8.12 (HVOUT11)
U7-T6LDP: R28.2, U8.3 (HVOUT20)
U7-T6LDP1: R28.1, T6.LDP
U7-T6RDP: R27.2, U8.14 (HVOUT9)
U7-T6RDP1: R27.1, T6.RDP
U7-T7K0: T7.K0, U8.1 (HVOUT22)
U7-T7K1: T7.K1, U8.36 (HVOUT31)
U7-T7K2: T7.K2, U8.37 (HVOUT30)
U7-T7K3: T7.K3, U8.38 (HVOUT29)
U7-T7K4: T7.K4, U8.39 (HVOUT28)
U7-T7K5: T7.K5, U8.40 (HVOUT27)
U7-T7K6: T7.K6, U8.41 (HVOUT26)
U7-T7K7: T7.K7, U8.42 (HVOUT25)
U7-T7K8: T7.K8, U8.43 (HVOUT24)
U7-T7K9: T7.K9, U8.44 (HVOUT23)
U7-T7LDP: R30.2, U8.35 (HVOUT32)
U7-T7LDP1: R30.1, T7.LDP
U7-T7RDP: R29.2, U8.2 (HVOUT21)
U7-T7RDP1: R29.1, T7.RDP

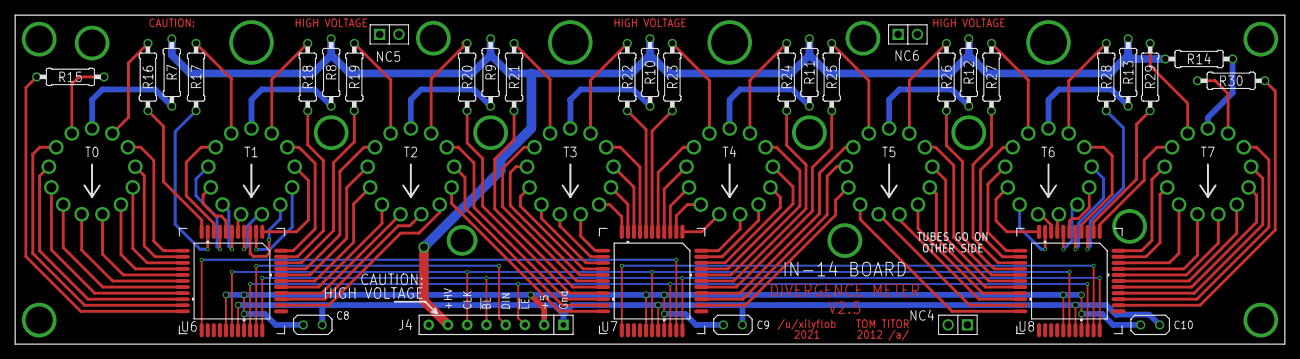
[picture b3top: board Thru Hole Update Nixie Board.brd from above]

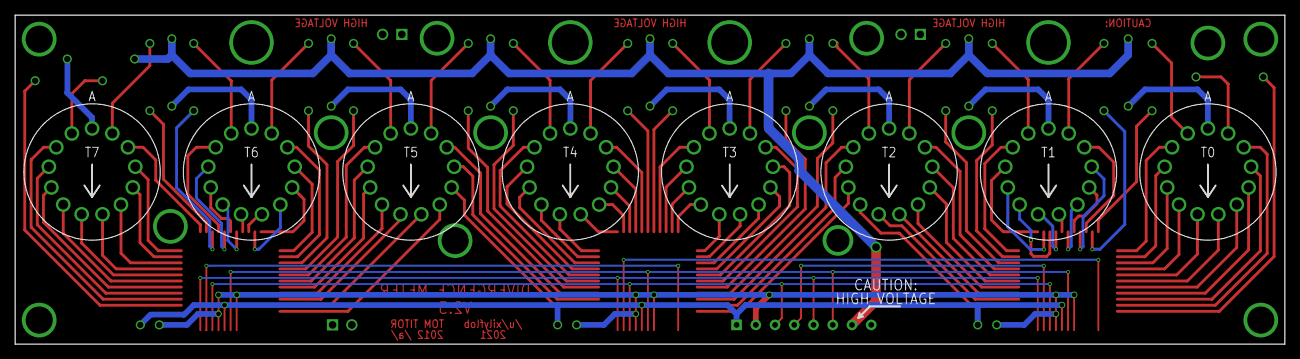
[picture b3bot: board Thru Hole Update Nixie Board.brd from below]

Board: 2 copper layers, 167.6 x 43.4 mm, 42 parts (8 on the bottom side), 129 nets.

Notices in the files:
mcc_generated_files/pin_manager.h:
(c) 2018 Microchip Technology Inc. and its subsidiaries.
parts and their libraries:
COPYRIGHT: Copyright (C) 2018 Accelerated Designs. All rights reserved
